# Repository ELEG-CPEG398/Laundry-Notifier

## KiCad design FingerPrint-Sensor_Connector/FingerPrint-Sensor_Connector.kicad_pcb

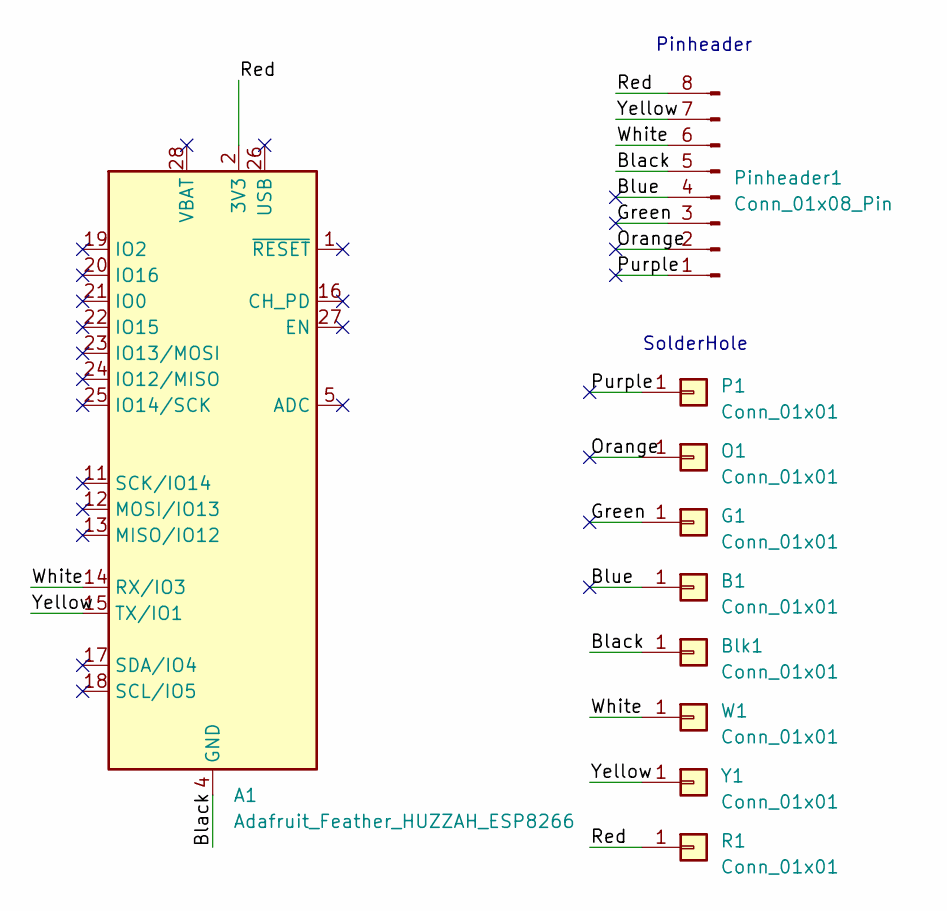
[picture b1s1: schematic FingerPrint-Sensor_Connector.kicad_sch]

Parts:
A1: Adafruit_Feather_HUZZAH_ESP8266; Adafruit_Feather_WithMountingHoles
B1: Conn_01x01; SolderWire-0.75sqmm_1x01_D1.25mm_OD2.3mm
Blk1: Conn_01x01; SolderWire-0.75sqmm_1x01_D1.25mm_OD2.3mm
G1: Conn_01x01; SolderWire-0.75sqmm_1x01_D1.25mm_OD2.3mm
O1: Conn_01x01; SolderWire-0.75sqmm_1x01_D1.25mm_OD2.3mm
P1: Conn_01x01; SolderWire-0.75sqmm_1x01_D1.25mm_OD2.3mm
Pinheader1: Conn_01x08_Pin; PinHeader_1x08_P2.54mm_Vertical
R1: Conn_01x01; SolderWire-0.75sqmm_1x01_D1.25mm_OD2.3mm
W1: Conn_01x01; SolderWire-0.75sqmm_1x01_D1.25mm_OD2.3mm
Y1: Conn_01x01; SolderWire-0.75sqmm_1x01_D1.25mm_OD2.3mm

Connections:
/Black: A1.4 (GND), Blk1.1, Pinheader1.5
/Blue: B1.1, Pinheader1.4
/Green: G1.1, Pinheader1.3
/Orange: O1.1, Pinheader1.2
/Purple: P1.1, Pinheader1.1
/Red: A1.2 (3V3), Pinheader1.8, R1.1
/White: A1.14 (RX/IO3), Pinheader1.6, W1.1
/Yellow: A1.15 (TX/IO1), Pinheader1.7, Y1.1

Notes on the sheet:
SolderHole
Pinheader

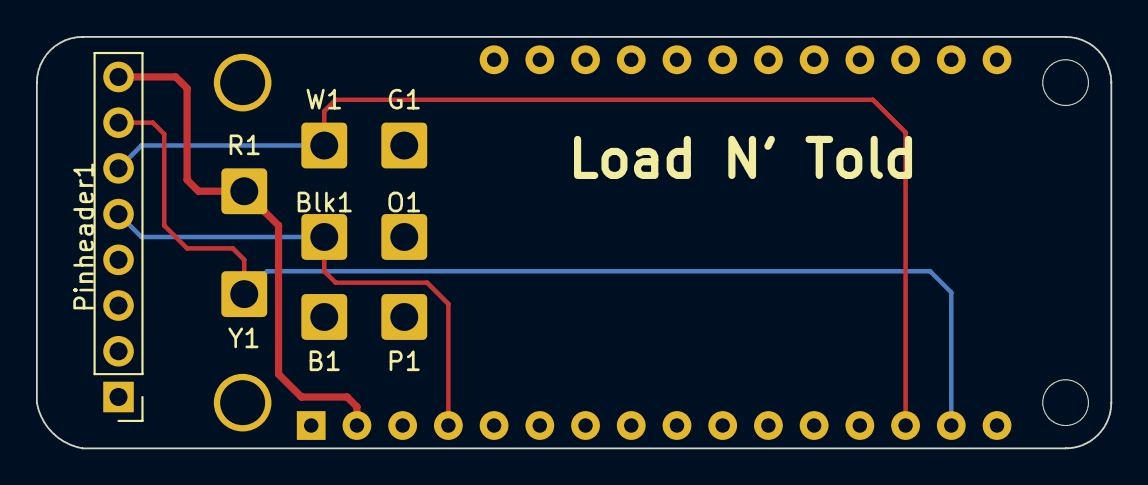
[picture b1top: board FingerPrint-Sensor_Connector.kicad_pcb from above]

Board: 2 copper layers, 59.7 x 22.9 mm, 10 parts (0 on the bottom side), 8 nets.

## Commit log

2024-04-08 Connection between app and esp8266
2024-04-11 difference method
2024-04-11 new system
    Detecting vibration based on average movement deviating from the average
2024-04-12 updated vibration detect boolean
2024-04-15 Working on Push Notifications via OneSignal
    -Config file with data separated
2024-04-18 Add files via upload
    Preemptive case. Need to change height once I see how tall everything is stacked up. Also need to cut it into two components and add a way to attach them together.
2024-04-19 Integrated OLED and IoT
2024-04-19 Fingerprint enroll example with workaround for issue I was experiencing
    Not sure how to fix the underlying issue right now but this works if we can't figure it out.
2024-04-19 message and receive from message feed
2024-04-19 Implemented OLED into main program
2024-04-19 Create Laundry_Notifier.aia
    -Scrapped Work
    -Allows communication between the ESP8266 and the android app
    -Reason for Scrapping: Push notifications aren't easily accessible, but should work in theory using Onesignal
2024-04-19 Updated OLED
    -Added wait screen to Start Menu
2024-04-20 Uses rms to detect vibrations
2024-04-20 Uses standard deviation to detect vibration
2024-04-20 Fingerprint Sensor PCB
    -PCB designed to connect the fingerprint to the feather stack.
    -Uses either pin headers or soldered wires for connections
2024-04-21 logo
2024-04-22 Initialize Vibration Sensor
    Initial setup for vibration sensor integration
2024-04-23 integrating vibration sensing
2024-04-25 working on load detection
2024-04-25 Create get_finger_workaround
    Get fingerprint ID example with workaround
2024-04-25 Rename get_finger_workaround to get_finger_workaround.ino
2024-04-25 Integration
    - bug fix: forgot to run vibrationsensorsetup function
2024-04-25 Vibration Sensor and Main
    - Detects load and only changes screens after a specified time perio
2024-04-25 Fingerprint sensor
    adjusted pins to work with ESP8266
2024-04-25 WIP Calibration menu
2024-04-27 bug fix
    -fixed bug
    -slight oled adjustments
2024-04-27 beginning fingerprint integration
    - bug: fingerprint sensor isn't detected upon integration
    - setup for function now return true when they fail
2024-04-27 working on fingerprint
    bug: OLED and fingerprint conflict
2024-04-27 fingerprint match and main
2024-04-27 fingerprint menu
2024-04-28 Update OLED_Display.h
    Added a flag to track if the display needs updating.
2024-04-28 Update OLED_Display.ino
    The display is only updated when absolutely necessary, which can help in reducing unnecessary processing and power consumption.
2024-04-29 Claim Load Implemented
2024-04-29 initialize enroll fingerprint integration
    -needs further testing
    -user's name needs to be saved
2024-04-30 slight changes
2024-05-02 json WIP
2024-05-02 Fingerprint Usernames stored
    - Uses ArduinoJson library to store fingerprint id # with user name
    - jsonString is a string of the json file
    - jsonString can be converted to JsonDocument type and vice versa
    - JsonDocument type is stored in Arduino Cloud as string variable jsonString
2024-05-02 Kodular App
    -Kodular App that uses a local ESP8266 server to communicate between the app and the Adafruit Huzzah
    - No longer in use due to difficulties in push notification
2024-05-02 Bug fix and Threshold Cloud
    -Threshold variable is now stored in cloud
    - Bug Fix: Arduino Cloud doesn't connect in time to initialize variables. A Delay was needed
2024-05-16 Logo Revision
